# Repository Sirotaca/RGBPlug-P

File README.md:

# RGBPlug Type P
Compact DE-15 ("VGA") adapter for the PlayStation AV multi-out. Video timing is unchanged, so a monitor or video processor compatible with 15 kHz RGB is required. The switch toggles between separate H/V sync or composite sync output.

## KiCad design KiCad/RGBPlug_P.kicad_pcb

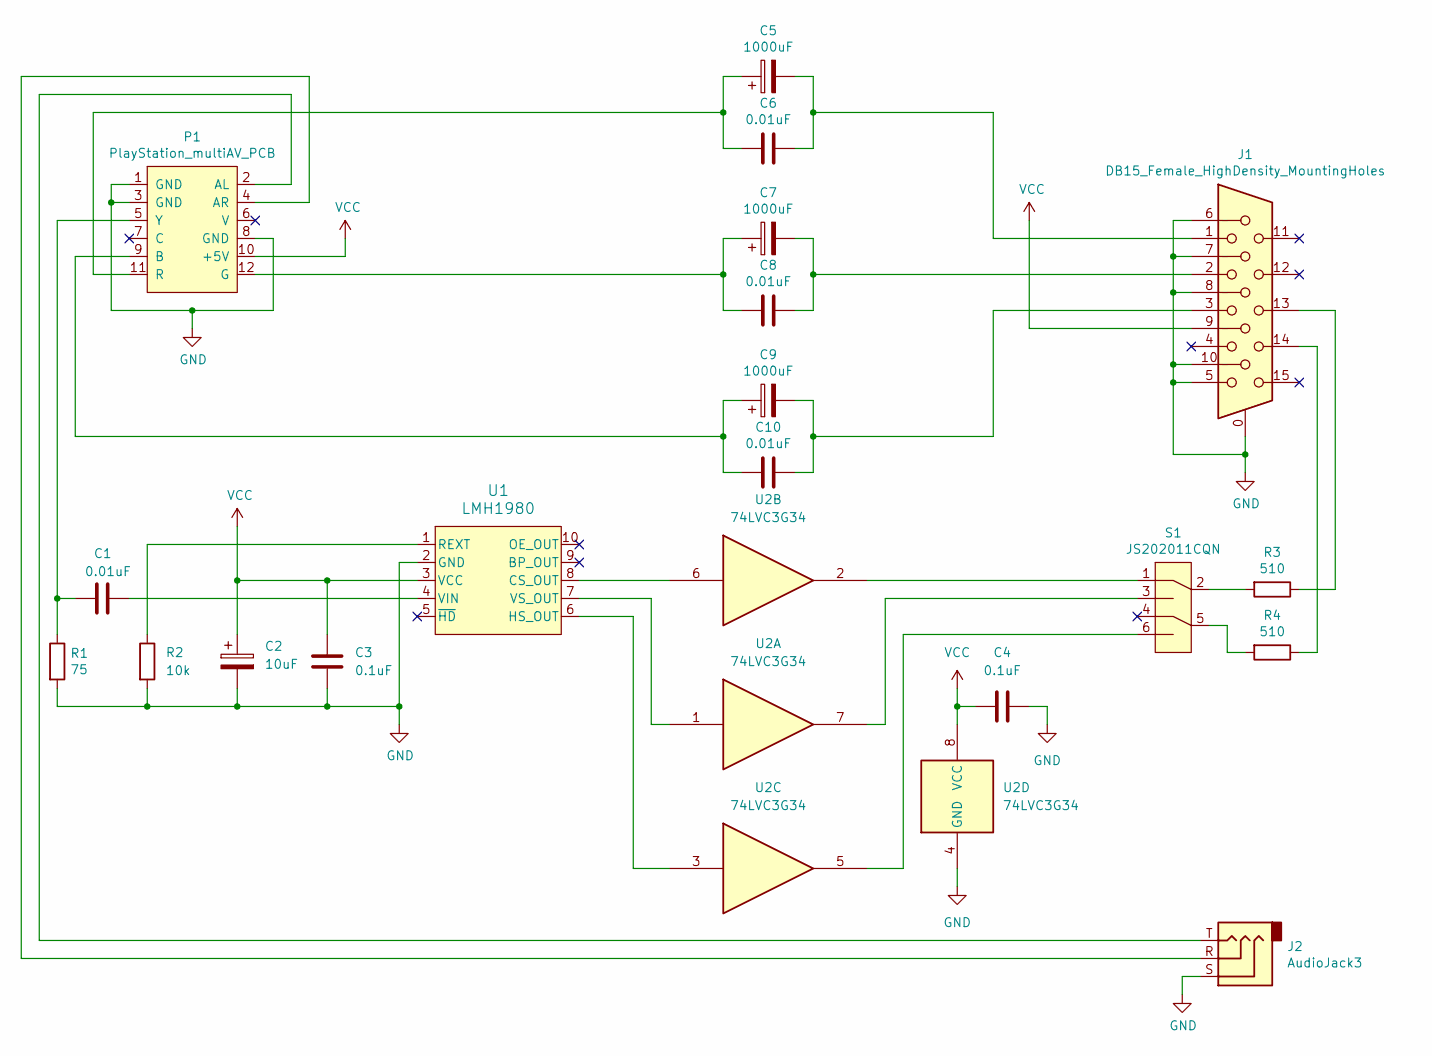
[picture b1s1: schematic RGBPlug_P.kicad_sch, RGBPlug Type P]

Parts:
C1, C6, C8, C10: 0.01uF; C_0805_2012Metric_Pad1.18x1.45mm_HandSolder
C2: 10uF; C_1206_3216Metric_Pad1.33x1.80mm_HandSolder
C3, C4: 0.1uF; C_0805_2012Metric_Pad1.18x1.45mm_HandSolder
C5, C7, C9: 1000uF; CP_Radial_D6.3mm_P2.50mm
J1: DB15_Female_HighDensity_MountingHoles; L17HTHES4F1C
J2: AudioJack3; Jack_3.5mm_CUI_SJ1-3533NG_Horizontal
P1: PlayStation_multiAV_PCB
R1: 75; R_0805_2012Metric_Pad1.20x1.40mm_HandSolder
R2: 10k; R_0805_2012Metric_Pad1.20x1.40mm_HandSolder
R3, R4: 510; R_0805_2012Metric_Pad1.20x1.40mm_HandSolder
S1: JS202011CQN; SW_CuK_JS202011CQN_DPDT_Straight
U1: LMH1980; VSSOP-10_3x3mm_P0.5mm
U2: 74LVC3G34; TSSOP-8_3x3mm_P0.65mm

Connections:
GND: C2.2, C3.2, C4.2, J1.0, J1.5, J1.6, J1.7, J1.8, J1.10, J2.S, P1.1 (GND), P1.3 (GND), P1.8 (GND), R1.2, R2.2, U1.2 (GND), U2.4 (GND)
unnamed: C5.2, C6.1, J1.1
unnamed: C7.2, C8.1, J1.2
unnamed: C9.2, C10.1, J1.3
unnamed: J1.13, R3.1
unnamed: J1.14, R4.1
unnamed: J2.T, P1.2 (AL)
unnamed: J2.R, P1.4 (AR)
unnamed: C9.1, C10.2, P1.9 (B)
unnamed: C7.1, C8.2, P1.12 (G)
unnamed: C5.1, C6.2, P1.11 (R)
unnamed: C1.1, P1.5 (Y), R1.1
unnamed: R3.2, S1.2
unnamed: R4.2, S1.5
unnamed: S1.1, U2.2
unnamed: S1.3, U2.7
unnamed: S1.6, U2.5
unnamed: U1.8 (CS_OUT), U2.6
unnamed: U1.6 (HS_OUT), U2.3
unnamed: R2.1, U1.1 (REXT)
unnamed: C1.2, U1.4 (VIN)
unnamed: U1.7 (VS_OUT), U2.1
VCC: C2.1, C3.1, C4.1, J1.9, P1.10 (+5V), U1.3 (VCC), U2.8 (VCC)

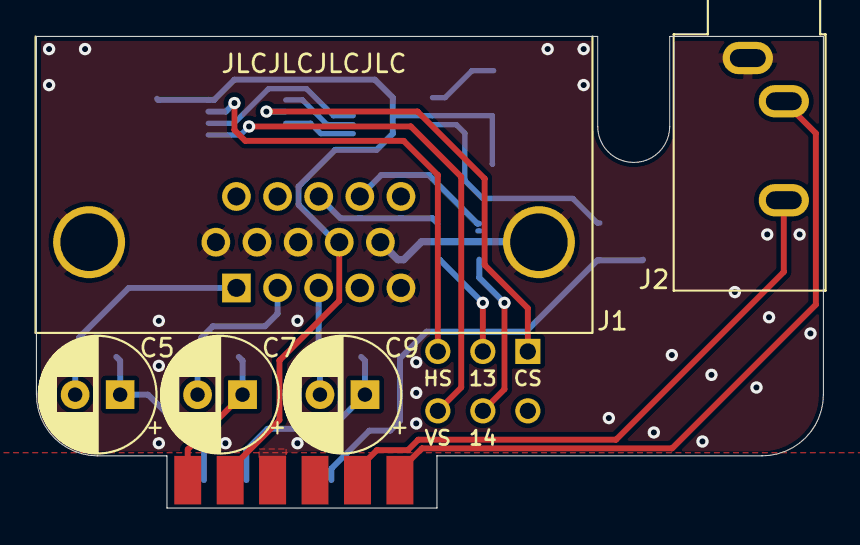
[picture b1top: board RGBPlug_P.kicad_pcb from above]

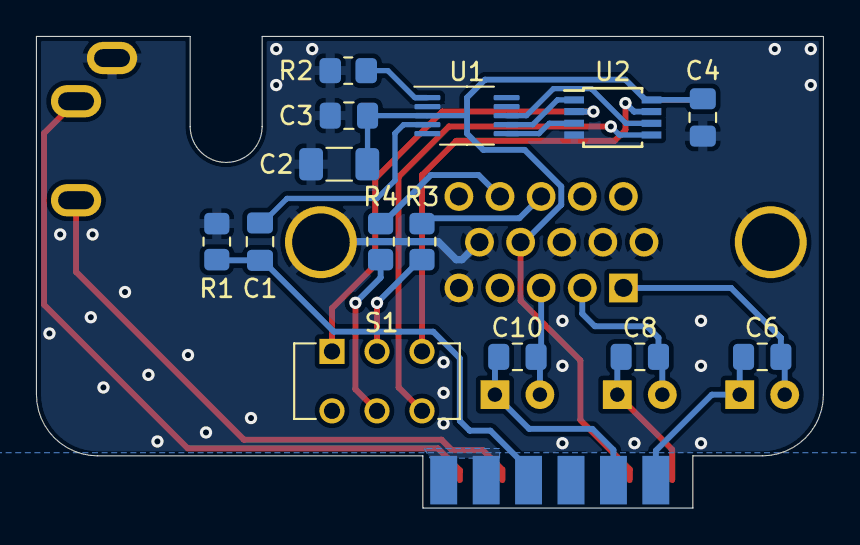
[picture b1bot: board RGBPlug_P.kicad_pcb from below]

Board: 2 copper layers, 43.7 x 26.2 mm, 20 parts (14 on the bottom side), 23 nets.

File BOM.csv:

"Reference","Value","Datasheet","Footprint","Qty","DNP"
"C1,C6,C8,C10","0.01uF","~","Capacitor_SMD:C_0805_2012Metric_Pad1.18x1.45mm_HandSolder","4",""
"C2","10uF","~","Capacitor_SMD:C_1206_3216Metric_Pad1.33x1.80mm_HandSolder","1",""
"C3,C4","0.1uF","~","Capacitor_SMD:C_0805_2012Metric_Pad1.18x1.45mm_HandSolder","2",""
"C5,C7,C9","1000uF","~","Capacitor_THT:CP_Radial_D6.3mm_P2.50mm","3",""
"J1","DB15_Female_HighDensity_MountingHoles","~","retro_gaming:L17HTHES4F1C","1",""
"J2","AudioJack3","~","Connector_Audio:Jack_3.5mm_CUI_SJ1-3533NG_Horizontal","1",""
"P1","PlayStation_multiAV_PCB","","retro_gaming:PlayStation_multiAV_PCB","1",""
"R1","75","~","Resistor_SMD:R_0805_2012Metric_Pad1.20x1.40mm_HandSolder","1",""
"R2","10k","~","Resistor_SMD:R_0805_2012Metric_Pad1.20x1.40mm_HandSolder","1",""
"R3,R4","510","~","Resistor_SMD:R_0805_2012Metric_Pad1.20x1.40mm_HandSolder","2",""
"S1","JS202011CQN","https://www.ckswitches.com/media/1422/js.pdf","Button_Switch_THT:SW_CuK_JS202011CQN_DPDT_Straight","1",""
"U1","LMH1980","LMH1980","Package_SO:VSSOP-10_3x3mm_P0.5mm","1",""
"U2","74LVC3G34","http://www.ti.com/lit/sg/scyt129e/scyt129e.pdf","Package_SO:TSSOP-8_3x3mm_P0.65mm","1",""
